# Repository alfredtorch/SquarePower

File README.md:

__handy, micro power supply__ to drive your projects in all kind of situations! SquarePower fits in any toolbox and in any invention

* connects to an USB-C source, old laptop charger, ... (max 24V)
* outputs a fixed (1,8 V 2,5 V 3,3 V 5V 9V 12V), an adjustable voltage settings (0,8-17V) or simply redirects Vin to Vout
* up to a current 2,1A (max 3A - needs cooling)
* all these specs runs on two separate DCDC converters.. true dual output capable!

# 💊 Features 
__🛒 Easy to source__ : COTS-Principle for cost-efficient creating and repairing</br>
__♻️ Reuse__ : give a second life to your cables and chargers</br>
__🧩 Size__ : weights a few grams fits in +- 30x30x30cm space</br>
__💪🏽 Capable dual output__ : individual On/Off Switch, thermal and shortcircuit protection</br>
__🕶 Flexible__ : runs from a power bank, car battery, wall adaptor</br>
__🪛 DIY Friendly__ : design files & tutorials available</br>

More information about the DCDC Converter can be found [here](https://protosupplies.com/product/mp2315-mini-adjustable-dc-dc-step-down-module/)

# 🔦 Explanation

## 🗺 Design Files

Designed in Eagle, in a messy way! Sorry! The related files are available under /Hardware.
Name | Description 
--- | ---
SQUAREPOWERV2 | VIN Vartions :</br>Jack, 3.5mm, horizontal, USB-C Trigger straight, below PCB
SQUAREPOWERVerticalUSBCV1 | VIN Vartions :</br> PCB USB-C right standing or straight, large pads for direct cable soldering

You can order a prepared 10x10cm Panel version directly from DirtyPCB from here. You get a bunch a squarepower pcbs but also a few handy pcb for re-routing 3pin signals, voltage divider and power distributor.

## 🛠 For DIY'er:
All you need are steady hands for the soldering part. Small SMD (Surface Mount) components can be tricky to solder for beginners.

## 💰BOM

Bill Of Material: Prices are estimated. Depending on your needs and suppliers, you can cut down the cost so that for one module you will spent less then 3€.

Part Name | Quantity | Price | Supply Link | Notes 
--- | --- | --- | --- | ---
PCB | 1x | 0,3€ | [DirtyPCB](https://dirtypcbs.com/store/designer/details/3748/6558/squarepower10x10panelv1-zip) | Order your own or create the complete manufacturing process on your own 
Mini DCDC | 2x | 1€ | [Aliexpress](https://s.click.aliexpress.com/e/_9hSzDv) | should be based on IC [MP2315](https://www.openhacks.com/uploadsproductos/datasheet_77.pdf)

### Optional components
In case, you don't need any fancy control or feedback but only a way to hack together a DCDC converter, you don't need any of these parts below.

Part Name | Quantity | Price | Supply Link | Notes 
--- | --- | --- | --- | ---
Screw Terminal 4 PIN | 3x | 0,40€ | [Aliexpress](https://s.click.aliexpress.com/e/_9jdwp1) | 2.54mm needs to be 4 pin - KF128
Mini Switch | 2x | 0,1€ | [Aliexpress](https://s.click.aliexpress.com/e/_A2f847) | Carefull, don't stress too much that component
LED | 2x | 0,10€ | [Aliexpress](https://s.click.aliexpress.com/e/_9vGqof) | 0805 - red, white, green... 
Resistors | 3x | 0,1€ | [Aliexpress](https://s.click.aliexpress.com/e/_A0ikLN) | 0805 - I would go for 1kΩ

### Variation : Removable or soldered DCDC converter 
Part Name | Quantity | Price | Supply Link | Notes 
--- | --- | --- | --- | ---
① Screw Terminal 4 PIN | 2x | 0,40€ | [Aliexpress](https://s.click.aliexpress.com/e/_A7x3ar) | 2.54mm needs to be 4 pin - KF128
② Pin header male right angle | 2x | 0,40€ | [Aliexpress](https://s.click.aliexpress.com/e/_9yioMn) | 2.54mm needs to be 4 pin - solder first the dcdc and pin header, before soldering it to the main pcb.

### Variation : Vout Terminals
Part Name | Quantity | Price | Supply Link | Notes 
--- | --- | --- | --- | ---
① Plug Screw Terminal | 2x | 0,30€ | [Aliexpress](https://s.click.aliexpress.com/e/_A9i5w7) | 3.5mm needs to be 2 pin - KF2EDG </br>can be straight or right angle **_OR_**            
② Screw Terminal | 2x | 0,30€ | [Aliexpress](https://s.click.aliexpress.com/e/_9GXJgJ) | 3.5mm needs to be 2 pin - KF350 **_OR_**       
② Screw Terminal 2.54mm | 2x | 0,30€ | [Aliexpress](https://s.click.aliexpress.com/e/_A7x3ar) | 2.54mm needs to be 2 pin - KF128 or JST XH etc...  

### Variation : Vin Terminals
Part Name | Quantity | Price | Supply Link | Notes 
--- | --- | --- | --- | ---
① Plug Screw Terminal| 2x | 0,30€ | [Aliexpress](https://s.click.aliexpress.com/e/_A9i5w7) | 3.5mm needs to be 2 pin - KF2EDG</br>can be straight or right angle **_OR_**
② Screw Terminal | 2x | 0,30€ | [Aliexpress](https://s.click.aliexpress.com/e/_AYf4Zd) | 3.5mm needs to be 2 pin - KF350</br>can be straight or right angle **_OR_**   
③ USB-C Trigger | 1x | 1,00€ | [Aliexpress](https://s.click.aliexpress.com/e/_9x3zGj) | best results with 20V Version **_OR_**       
⓸ Power Jack | 1x | 0,30€ | [Aliexpress](https://s.click.aliexpress.com/e/_9gR5cj) | 5.5x2.1mm DC-005

🙏 Please if you need to shop for parts, it would be great that you use the supply links below. As they are affilated, you're supporting me directly to continue to deliver new projects to the community! Thank you!
At the moment I have no possibility for a larger production and distribution. Of course, I am ready for any cooperation to industrialize the production.</br>  
 Available on [Tindie](https://www.tindie.com/products/alfredtorch/square-power/)</br>
## 👨🏼‍🏫Tutorials
Soon updates for:
* How to build your own & first steps
* Discover Ohm's Law with an USB Power Meter

## ✔ToDo
- [x] Redesign connections so the switches are symmetrical
- [ ] Add some space for soldering screw terminal right in place
- [ ] Add some tutorials about making and using!
- [ ] Design a nice laser-cutted and 3D printed enclosure
- [ ] Test if possible to arduino-drive the Enable Pin with a BSS138 Level Shifter
- [x] Datasheet : Add 100k Resistor between Vin<--Switch-->Enable Pin

## Licence
This work is licensed under Creative Commons License </br>

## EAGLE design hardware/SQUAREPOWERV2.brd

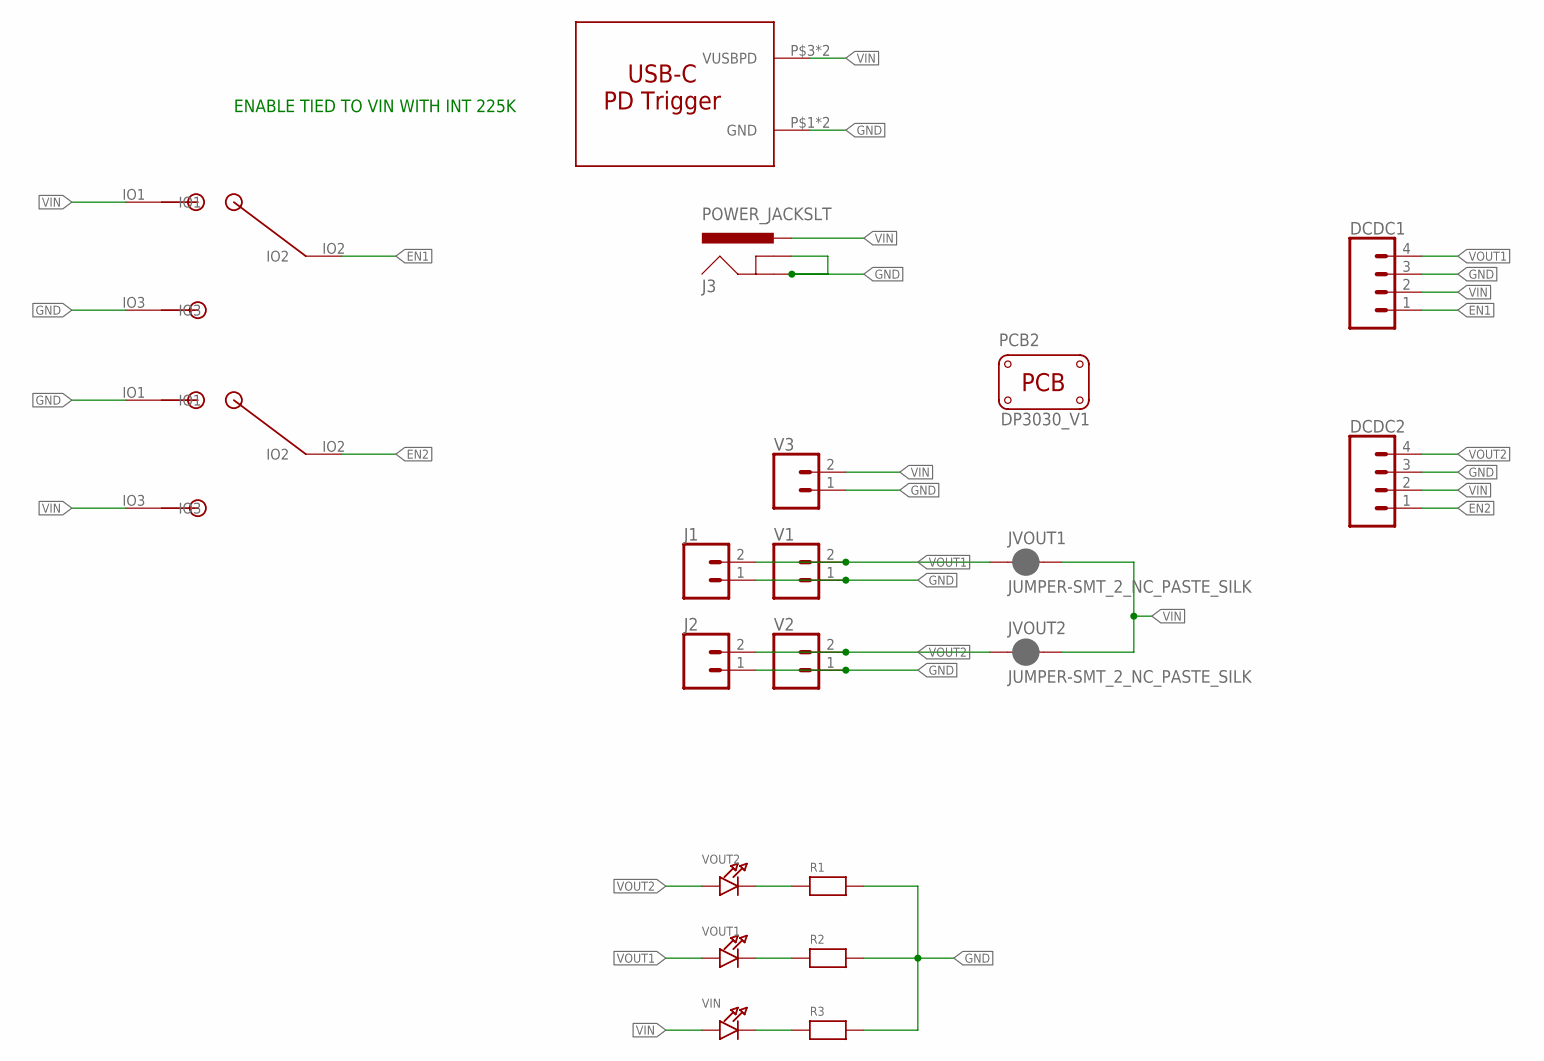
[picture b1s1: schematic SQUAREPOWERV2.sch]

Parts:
DCDC1, DCDC2: CONN_04LONGPADS; 1X04_LONGPADS
J1, J2: CONN_02; 1X02
J3: POWER_JACKSLT; POWER_JACK_SLOT
JVOUT1, JVOUT2: JUMPER-SMT_2_NC_PASTE_SILK; SMT-JUMPER_2_NC_PASTE_SILK
PCB2: PCB_DP_SQUARE-3X3; DP3030_V1
R1, R2, R3: RESISTOR0805; 0805
U$1, U$2: SPDT-SWITCH-MSKT-12C00; MSKT-12C00
U$5: USB_PD_TRIGGER; USB-PDTRIGGER
V1, V2, V3: CONN_023.5MM; SCREWTERMINAL-3.5MM-2
VIN: LED0805; CHIPLED_0805
VOUT1, VOUT2: LED0805; CHIPLED_0805

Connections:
EN1: DCDC1.1, U$1.IO2
EN2: DCDC2.1, U$2.IO2
GND: DCDC1.3, DCDC2.3, J1.1, J2.1, J3.GND@1 (GNDBREAK), J3.GND@2 (GND), R1.2, R2.2, R3.2, U$1.IO3, U$2.IO1, U$5.P$1 (GND), U$5.P$2 (GND), V1.1, V2.1, V3.1
unnamed: R1.1, VOUT2.C
unnamed: R2.1, VOUT1.C
unnamed: R3.1, VIN.C
VIN: DCDC1.2, DCDC2.2, J3.PWR, JVOUT1.2, JVOUT2.2, U$1.IO1, U$2.IO3, U$5.P$3 (VUSBPD), U$5.P$4 (VUSBPD), V3.2, VIN.A
VOUT1: DCDC1.4, J1.2, JVOUT1.1, V1.2, VOUT1.A
VOUT2: DCDC2.4, J2.2, JVOUT2.1, V2.2, VOUT2.A

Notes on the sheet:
ENABLE TIED TO VIN WITH INT 225K

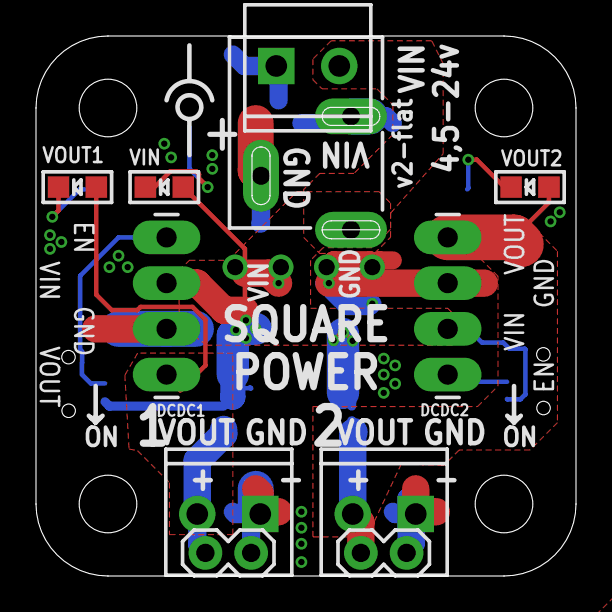
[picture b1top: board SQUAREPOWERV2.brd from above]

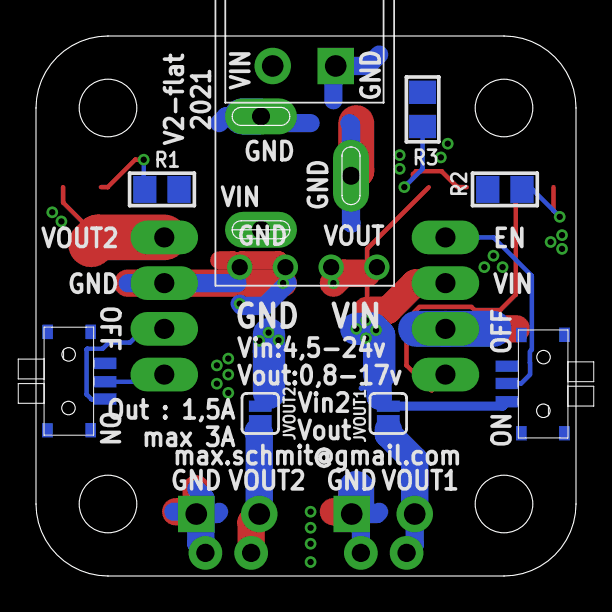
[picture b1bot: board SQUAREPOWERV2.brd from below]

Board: 2 copper layers, 30.0 x 30.0 mm, 20 parts (8 on the bottom side), 9 nets.

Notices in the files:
parts and their libraries:
SparkFun-Connectors: Licensing: Creative Commons ShareAlike 4.0 International - https://creativecommons.org/licenses/by-sa/4.0
microbuilder: This work is placed in the public domain, and may be freely used for commercial and non-commercial work with the following conditions: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
